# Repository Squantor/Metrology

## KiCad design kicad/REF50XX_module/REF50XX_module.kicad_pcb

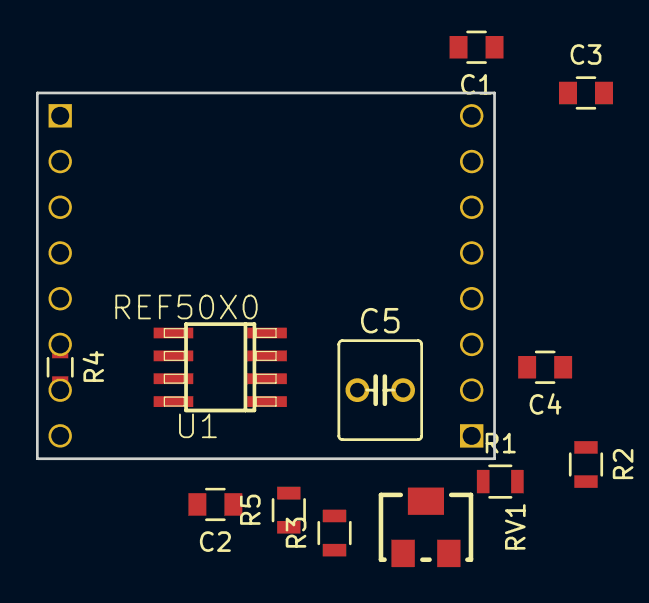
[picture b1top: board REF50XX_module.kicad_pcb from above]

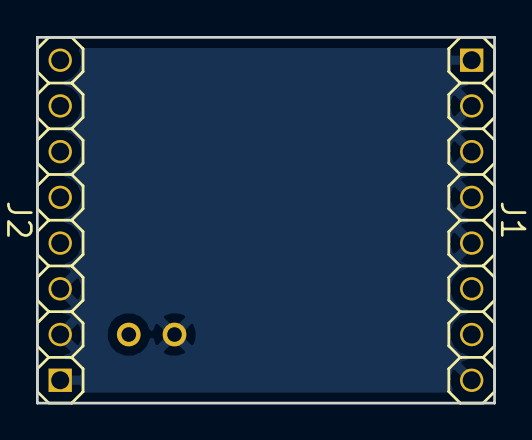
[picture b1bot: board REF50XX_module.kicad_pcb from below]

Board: 2 copper layers, 25.4 x 20.3 mm, 14 parts (2 on the bottom side), 11 nets, no tracks yet.

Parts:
C1, C2, C4: 1u; C_0805
C3: 10u; C_0805
C5: 4.7u; C025-055X046
J1, J2: PINS_1X8; Header-0254-1X08-H010
R1: 470k; R_0805
R2: 1; R_0805
R3: 1k; R_0805
R4: 0; R_0603
R5: 0; R_0805
RV1: 10k; POT_SMD_44W
U1: REF50X0; SquantorIC-SO08

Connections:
GND: C1.1, C2.2, C3.1, C4.1, C5.1, J1.1, J1.2, J1.3, J1.4, J1.5, J1.8, J2.1, J2.2, J2.3, R3.2, U1.4
HeaterGround: J2.6, J2.7
unnamed: C2.1, R1.2, U1.5
unnamed: C3.2, C5.2, R2.1
unnamed: R1.1, RV1.2
unnamed: R3.1, RV1.1
unnamed: R5.2, RV1.3
RefTemp: J2.4, U1.3
Sense: J1.6, R4.1
Vin: C1.2, J2.5, U1.2
Vref: C4.2, J1.7, R2.2, R4.2, R5.1, U1.6

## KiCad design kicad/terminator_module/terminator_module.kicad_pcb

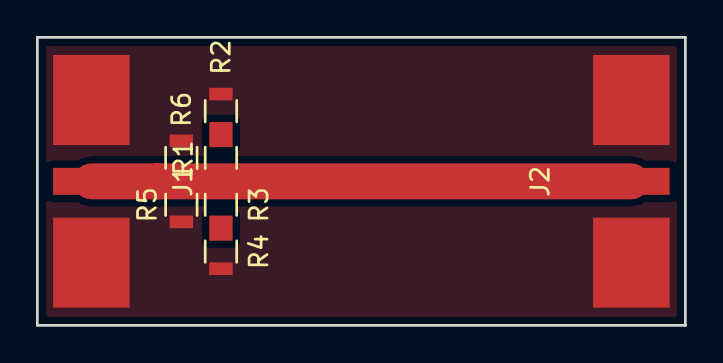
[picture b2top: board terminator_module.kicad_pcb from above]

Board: 2 copper layers, 36.0 x 16.0 mm, 8 parts (0 on the bottom side), 4 nets.

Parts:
J1, J2: Coax; coax_edge_1.5_center_5_side
R1, R2, R3, R4, R5, R6: R; R_0805

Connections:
GND: J1.1, J2.1, R2.2, R4.2, R5.2, R6.2
unnamed: J1.2, J2.2, R1.1, R3.1, R5.1, R6.1
unnamed: R1.2, R2.1
unnamed: R3.2, R4.1
